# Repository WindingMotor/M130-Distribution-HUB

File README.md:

# M130-Distribution-HUB

## Overview

The M130-Distribution-HUB provides centralized power distribution, relay control, and sensor interfacing for MoTeC M130 ECU-equipped race vehicles. Designed for Formula SAE competition with the Yamaha WR450F engine.

### Key Features

- **Direct MoTeC M130 Integration**: SuperSeal 34-pin and 26-pin connectors
- **4-Layer PCB Design**: Dual solid ground planes with optimized power distribution
- **Relay-Switched Outputs**: 4x automotive-grade SPDT relays with flyback protection
- **Individual Circuit Protection**: ATM fuse holders on each relay
- **Phoenix Contact Terminals**: Organized sensor and harness connection points
- **5V Power from MoTeC**: Eliminates need for external voltage regulation
- **FSAE Compliant**: Master shutdown relay, individual fusing, clear labeling

## Specifications

| Parameter | Value |
|-----------|-------|
| PCB Layers | 4 (Signal, GND, GND, Signal) |
| Copper Weight | 1oz (35µm) (On each layer) |
| Board Dimensions | ~120mm x 90mm |
| Max Continuous Current | 40A (Across all relays) |
| Operating Voltage | 12V nominal (8-16V range) |
| Relay Coil Voltage | 12V DC |
| Fuse Protection | ATM blade fuses (15-30A) |
| Operating Temperature | -40°C to +95°C |
| Connector Count | 2x SuperSeal, 6x Phoenix Contact |

## PCB Component BOM

| Reference | Component | Part Number | Value | Package | Quantity |
|-----------|-----------|-------------|-------|---------|----------|
| U1, U2, U3, U4 | Automotive Relay | BARK-S-112DM | 12V SPDT | Custom | 4 |
| D1, D2, D3, D4 | Flyback Diode | 1N5399 | 1.5A/1000V | DO-15 | 4 |
| F1, F2, F3, F4 | Fuse Holder | FUSE_3568 | ATM | Custom | 4 |
| CN0 | SuperSeal Connector | 6437288-3 | 34-pin + 2-pin | Custom | 1 |
| CN1-CN5 | Terminal Block | Phoenix 1190310 | 12-pos | Custom | 6 |

*Note: Fuses (15-30A ATM) not included on PCB -> user-supplied based on load requirements.*

## Relay Output Assignments

| Relay | Function | Typical Fuse Rating | Connected Load |
|-------|----------|---------------------|----------------|
| U1 | Master Relay | 30A | Main power distribution |
| U2 | Fuel Pump Relay | 15A | Fuel pump (WR450F) |
| U3 | Lights Relay | 10A | Extra / running lights |
| U4 | Radiator Fan Relay | 15A | Engine cooling fan |

## Power Distribution

The PCB receives 12V battery & alternator power and distributes it through relay-switched outputs with individual fusing:

```
12V_BATT → Master Relay → 12V_OUT_MASTER_RELAY → Individual Load Relays → Fused Outputs
                                                → Fuel Pump
                                                → Lights
                                                → Radiator Fan
```

**5V Power**: Supplied directly from MoTeC M130 ECU 5V sensor output (no onboard regulation required). (Has dual 5V outputs at 1A Max)

## Design Features

- **Via Stitching**: Comprehensive thermal and EMI management with 4-layer stitched vias on high-current relay zones
- **Dual Ground Planes**: Solid inner layers for signal integrity and low-impedance return paths
- **Differential Pair Routing**: For CAN bus and Ethernet
- **Universal Teardrops**: PCB designed fir vibration resistance for motorsports environments
- **EMI Shielding**: Grounding via fence between high-power traces and sensitive signals
- **Conformal Coating Ready**: PCB accommodates post assembly coating for extra environmental protection

## Assembly Notes

1. **Relay Orientation**: Ensure pin 1 alignment with PCB silkscreen markings
2. **Flyback Diode Polarity**: Cathode (banded end) toward relay coil positive terminal
3. **Fuse Selection**: Size fuses per load requirements (5-30A ATM blade)
4. **Conformal Coating**: Apply MG Chemicals 422B or equivalent after assembly
5. **Mounting**: Use rubber grommets at mounting holes for vibration isolation

## Usage

1. Connect MoTeC M130 ECU via 34-pin and 26-pin SuperSeal connectors
2. Wire battery 12V and alternator 12V to main power terminals
3. Install appropriate ATM fuses in each holder per load requirements
4. Connect sensors to Phoenix Contact terminal blocks
5. Wire relay outputs to vehicle loads (fuel pump, lights, fan)
6. Configure MoTeC M130 relay enable outputs (digital outputs)

## Testing

Before vehicle installation:
- **Continuity Check**: Verify all power and ground nets
- **Isolation Test**: Confirm >10MΩ resistance between power and ground
- **Relay Function**: Enable each relays coil, verify contact closure with multimeter
- **Fuse Ratings**: Confirm proper fuse installation for each circuit

## License

This project is licensed under the **CERN Open Hardware Licence Version 2 - Permissive** (CERN-OHL-P-2.0).

You are free to:
- Use commercially
- Modify
- Distribute
- Use in closed source, with notice of changes

See [LICENSE](LICENSE) file for full terms.

## Credits

**Designed by**: RAM Racing @ VCU Formula SAE Team  
**Main Designer**: Isaac Subudhi  
**Target Vehicle**: Yamaha WR450F IC Engine  
**ECU Platform**: MoTeC M130  
**Design Tool**: KiCad 9.0

## Support

For technical questions or contributions, please open an issue or pull request.

***

**Disclaimer**: This design is provided as-is for educational and motorsports purposes. Users are responsible for validating the design meets their specific application requirements and safety standards.

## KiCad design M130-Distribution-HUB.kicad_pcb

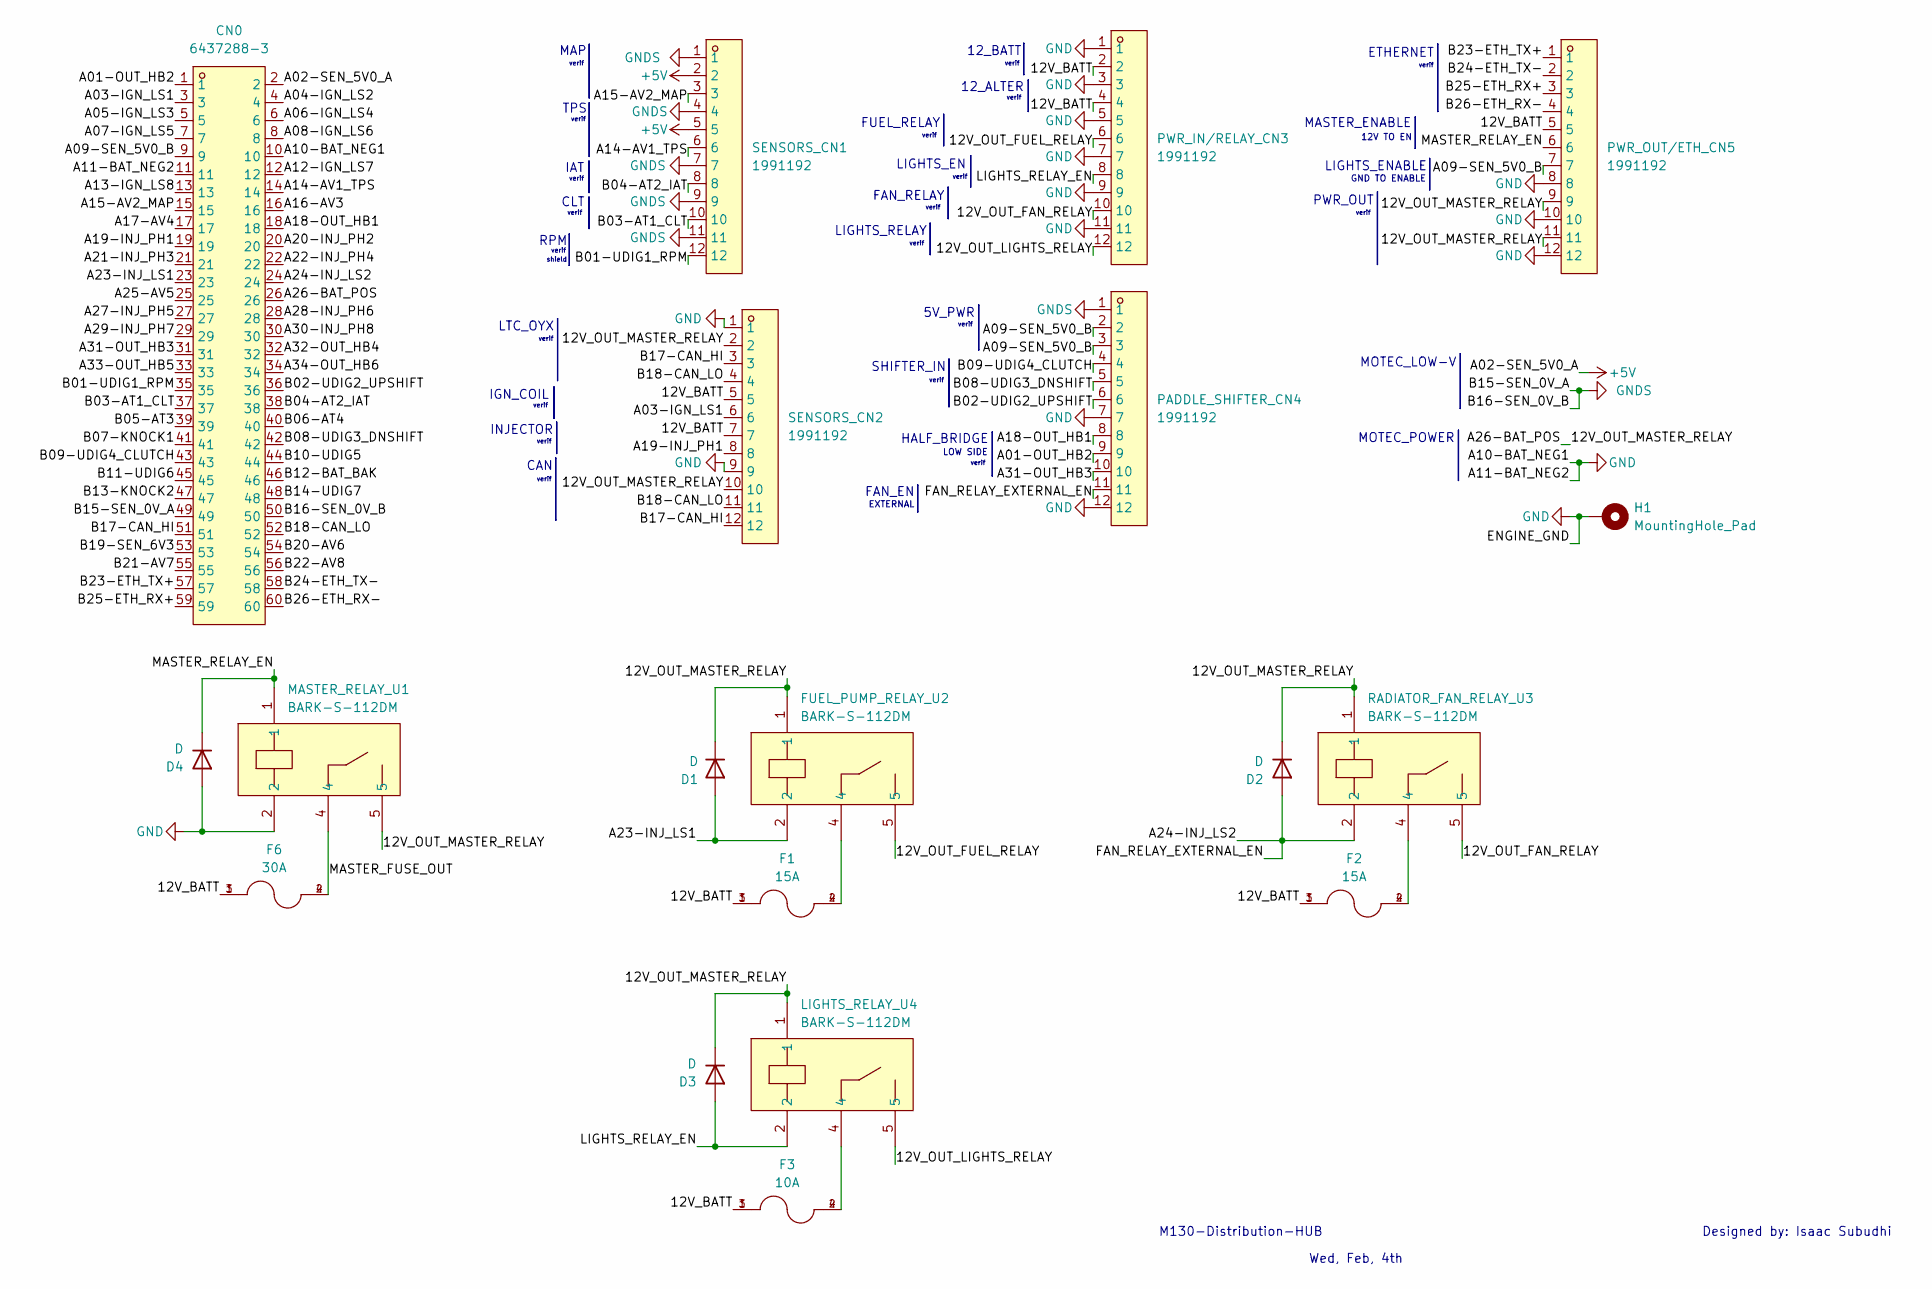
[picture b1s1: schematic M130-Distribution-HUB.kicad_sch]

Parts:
CN0: 6437288-3; DSUB-60P_SUPERSEAL; LCSC Part C591769
D1, D2, D3, D4: D; D_DO-15_P10.16mm_Horizontal
F1, F2: 15A; FUSE_3568; PARTREV C
F3: 10A; FUSE_3568; PARTREV C
F6: 30A; FUSE_3568; PARTREV C
FUEL_PUMP_RELAY_U2: BARK-S-112DM; RELAY-TH_BARK-S-112DM; LCSC Part C22385001
H1: MountingHole_Pad; MountingHole_5.3mm_M5_DIN965_Pad_TopBottom
LIGHTS_RELAY_U4: BARK-S-112DM; RELAY-TH_BARK-S-112DM; LCSC Part C22385001
MASTER_RELAY_U1: BARK-S-112DM; RELAY-TH_BARK-S-112DM; LCSC Part C22385001
PADDLE_SHIFTER_CN4: 1991192; PHOENIX_1991192; LCSC Part C3309553
PWR_IN/RELAY_CN3: 1991192; PHOENIX_1991192; LCSC Part C3309553
PWR_OUT/ETH_CN5: 1991192; PHOENIX_1991192; LCSC Part C3309553
RADIATOR_FAN_RELAY_U3: BARK-S-112DM; RELAY-TH_BARK-S-112DM; LCSC Part C22385001
SENSORS_CN1, SENSORS_CN2: 1991192; PHOENIX_1991192; LCSC Part C3309553

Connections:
+5V: CN0.2, SENSORS_CN1.2, SENSORS_CN1.5
/12V_BATT: F1.1, F1.3, F2.1, F2.3, F3.1, F3.3, F6.1, F6.3, PWR_IN/RELAY_CN3.2, PWR_IN/RELAY_CN3.4, PWR_OUT/ETH_CN5.5, SENSORS_CN2.5, SENSORS_CN2.7
/12V_OUT_FAN_RELAY: PWR_IN/RELAY_CN3.10, RADIATOR_FAN_RELAY_U3.5
/12V_OUT_FUEL_RELAY: FUEL_PUMP_RELAY_U2.5, PWR_IN/RELAY_CN3.6
/12V_OUT_LIGHTS_RELAY: LIGHTS_RELAY_U4.5, PWR_IN/RELAY_CN3.12
/12V_OUT_MASTER_RELAY: CN0.26, D1.1 (K), D2.1 (K), D3.1 (K), FUEL_PUMP_RELAY_U2.1, LIGHTS_RELAY_U4.1, MASTER_RELAY_U1.5, PWR_OUT/ETH_CN5.9, PWR_OUT/ETH_CN5.11, RADIATOR_FAN_RELAY_U3.1, SENSORS_CN2.2, SENSORS_CN2.10
/A01-OUT_HB2: CN0.1, PADDLE_SHIFTER_CN4.9
/A03-IGN_LS1: CN0.3, SENSORS_CN2.6
/A04-IGN_LS2: CN0.4
/A05-IGN_LS3: CN0.5
/A06-IGN_LS4: CN0.6
/A07-IGN_LS5: CN0.7
/A08-IGN_LS6: CN0.8
/A09-SEN_5V0_B: CN0.9, PADDLE_SHIFTER_CN4.2, PADDLE_SHIFTER_CN4.3, PWR_OUT/ETH_CN5.7
/A12-IGN_LS7: CN0.12
/A13-IGN_LS8: CN0.13
/A14-AV1_TPS: CN0.14, SENSORS_CN1.6
/A15-AV2_MAP: CN0.15, SENSORS_CN1.3
/A16-AV3: CN0.16
/A17-AV4: CN0.17
/A18-OUT_HB1: CN0.18, PADDLE_SHIFTER_CN4.8
/A19-INJ_PH1: CN0.19, SENSORS_CN2.8
/A20-INJ_PH2: CN0.20
/A21-INJ_PH3: CN0.21
/A22-INJ_PH4: CN0.22
/A23-INJ_LS1: CN0.23, D1.2 (A), FUEL_PUMP_RELAY_U2.2
/A24-INJ_LS2: CN0.24, D2.2 (A), PADDLE_SHIFTER_CN4.11, RADIATOR_FAN_RELAY_U3.2
/A25-AV5: CN0.25
/A27-INJ_PH5: CN0.27
/A28-INJ_PH6: CN0.28
/A29-INJ_PH7: CN0.29
/A30-INJ_PH8: CN0.30
/A31-OUT_HB3: CN0.31, PADDLE_SHIFTER_CN4.10
/A32-OUT_HB4: CN0.32
/A33-OUT_HB5: CN0.33
/A34-OUT_HB6: CN0.34
/B01-UDIG1_RPM: CN0.35, SENSORS_CN1.12
/B02-UDIG2_UPSHIFT: CN0.36, PADDLE_SHIFTER_CN4.6
/B03-AT1_CLT: CN0.37, SENSORS_CN1.10
/B04-AT2_IAT: CN0.38, SENSORS_CN1.8
/B05-AT3: CN0.39
/B06-AT4: CN0.40
/B07-KNOCK1: CN0.41
/B08-UDIG3_DNSHIFT: CN0.42, PADDLE_SHIFTER_CN4.5
/B09-UDIG4_CLUTCH: CN0.43, PADDLE_SHIFTER_CN4.4
/B10-UDIG5: CN0.44
/B11-UDIG6: CN0.45
/B12-BAT_BAK: CN0.46
/B13-KNOCK2: CN0.47
/B14-UDIG7: CN0.48
/B17-CAN_HI: CN0.51, SENSORS_CN2.3, SENSORS_CN2.12
/B18-CAN_LO: CN0.52, SENSORS_CN2.4, SENSORS_CN2.11
/B19-SEN_6V3: CN0.53
/B20-AV6: CN0.54
/B21-AV7: CN0.55
/B22-AV8: CN0.56
/B23-ETH_TX+: CN0.57, PWR_OUT/ETH_CN5.1
/B24-ETH_TX-: CN0.58, PWR_OUT/ETH_CN5.2
/B25-ETH_RX+: CN0.59, PWR_OUT/ETH_CN5.3
/B26-ETH_RX-: CN0.60, PWR_OUT/ETH_CN5.4
/LIGHTS_RELAY_EN: D3.2 (A), LIGHTS_RELAY_U4.2, PWR_IN/RELAY_CN3.8
/MASTER_FUSE_OUT: F6.2, F6.4, MASTER_RELAY_U1.4
/MASTER_RELAY_EN: D4.1 (K), MASTER_RELAY_U1.1, PWR_OUT/ETH_CN5.6
GND: CN0.10, CN0.11, D4.2 (A), H1.1, MASTER_RELAY_U1.2, PADDLE_SHIFTER_CN4.7, PADDLE_SHIFTER_CN4.12, PWR_IN/RELAY_CN3.1, PWR_IN/RELAY_CN3.3, PWR_IN/RELAY_CN3.5, PWR_IN/RELAY_CN3.7, PWR_IN/RELAY_CN3.9, PWR_IN/RELAY_CN3.11, PWR_OUT/ETH_CN5.8, PWR_OUT/ETH_CN5.10, PWR_OUT/ETH_CN5.12, SENSORS_CN2.1, SENSORS_CN2.9
GNDS: CN0.49, CN0.50, PADDLE_SHIFTER_CN4.1, SENSORS_CN1.1, SENSORS_CN1.4, SENSORS_CN1.7, SENSORS_CN1.9, SENSORS_CN1.11
unnamed: F1.2, F1.4, FUEL_PUMP_RELAY_U2.4
unnamed: F2.2, F2.4, RADIATOR_FAN_RELAY_U3.4
unnamed: F3.2, F3.4, LIGHTS_RELAY_U4.4

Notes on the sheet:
ETHERNET
LIGHTS_EN
FAN_RELAY
EXTERNAL
LOW SIDE
verif
HALF_BRIDGE
LIGHTS_RELAY
MASTER_ENABLE
LIGHTS_ENABLE
IGN_COIL
MAP
12_BATT
GND TO ENABLE
FUEL_RELAY
12_ALTER
Wed, Feb, 4th
12V TO EN
CAN
TPS
LTC_OYX
PWR_OUT
IAT
Designed by: Isaac Subudhi
shield
MOTEC_POWER
MOTEC_LOW-V
RPM
5V_PWR
M130-Distribution-HUB
SHIFTER_IN
FAN_EN
INJECTOR
CLT

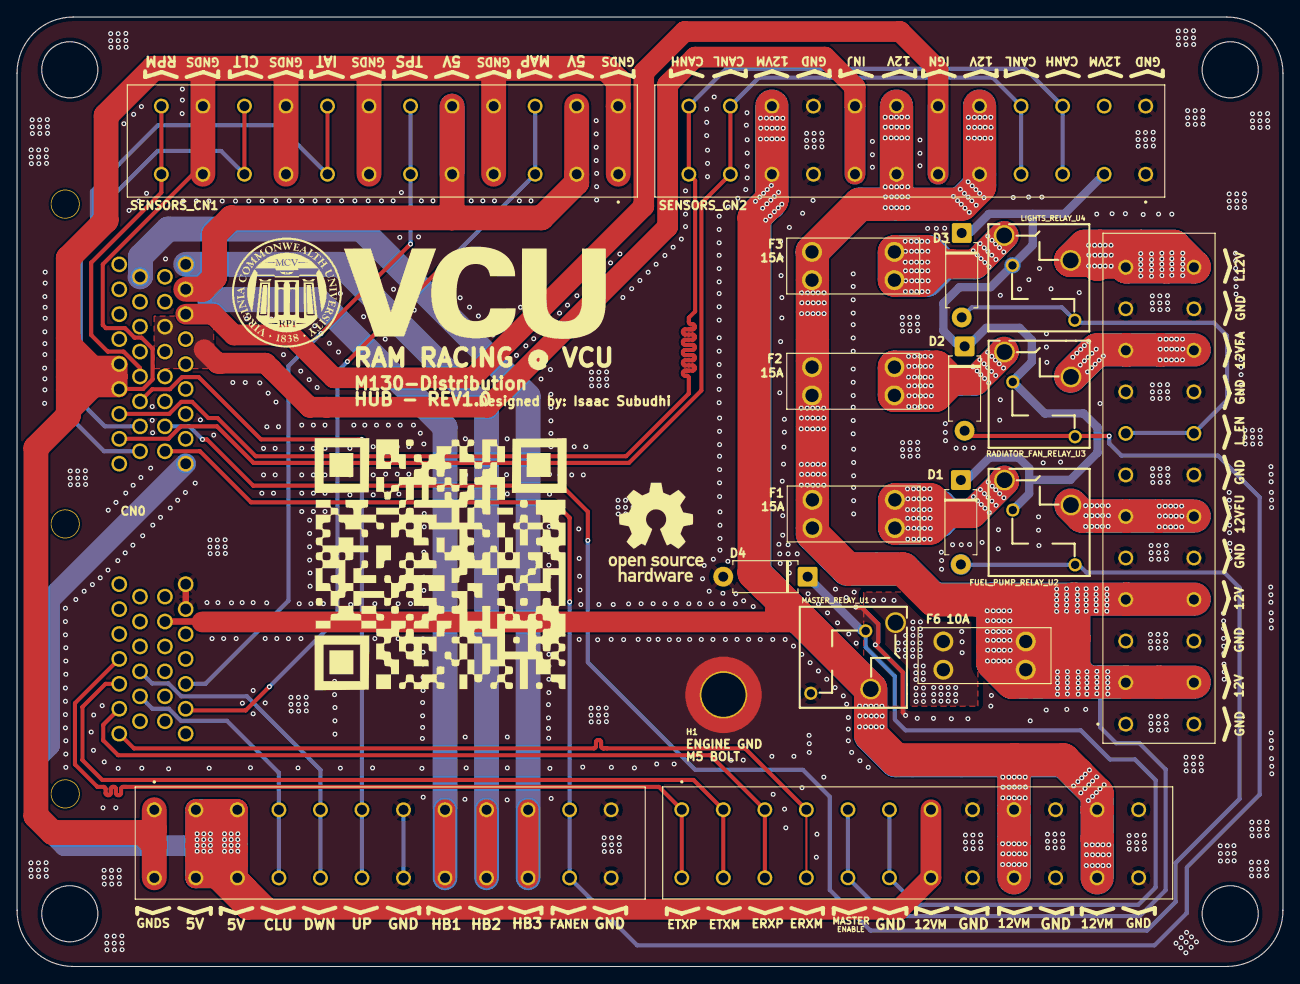
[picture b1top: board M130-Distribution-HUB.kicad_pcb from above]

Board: 4 copper layers, 152.4 x 114.3 mm, 19 parts (0 on the bottom side), 36 nets.

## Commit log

2025-11-13 Init Commt
2025-11-13 Readme v1
2025-11-13 readme fixed badges
2025-11-13 added license
2025-11-13 Engine GND bolt
2025-11-13 added image
2025-11-14 Top View and gerbers
2025-11-15 Minor changes
2025-11-15 Stich via adjustments
2025-12-04 Thermal relif
2025-12-04 lock
2026-01-14 Fixed DRC issues.
2026-01-15 Revise README for clarity
2026-01-15 Gitignore changes
2026-01-28 Moved to vertical connectors
2026-02-19 Slight changes
2026-03-07 slight board update

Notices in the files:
README.md:
License: CERN-OHL-P-2.0
